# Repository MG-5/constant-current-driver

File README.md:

# constant-current-driver
A constant current driver up to 1.5A to drive LEDs

### Requirements for rev 1.0
* efficient step-down converter, not linear
* high frequency
* cheap IC
* PWM control
* up to 1.5A in voltage range 5-24V output

### Known issues in rev 1.0
* none

### Pictures (rev 1.0)

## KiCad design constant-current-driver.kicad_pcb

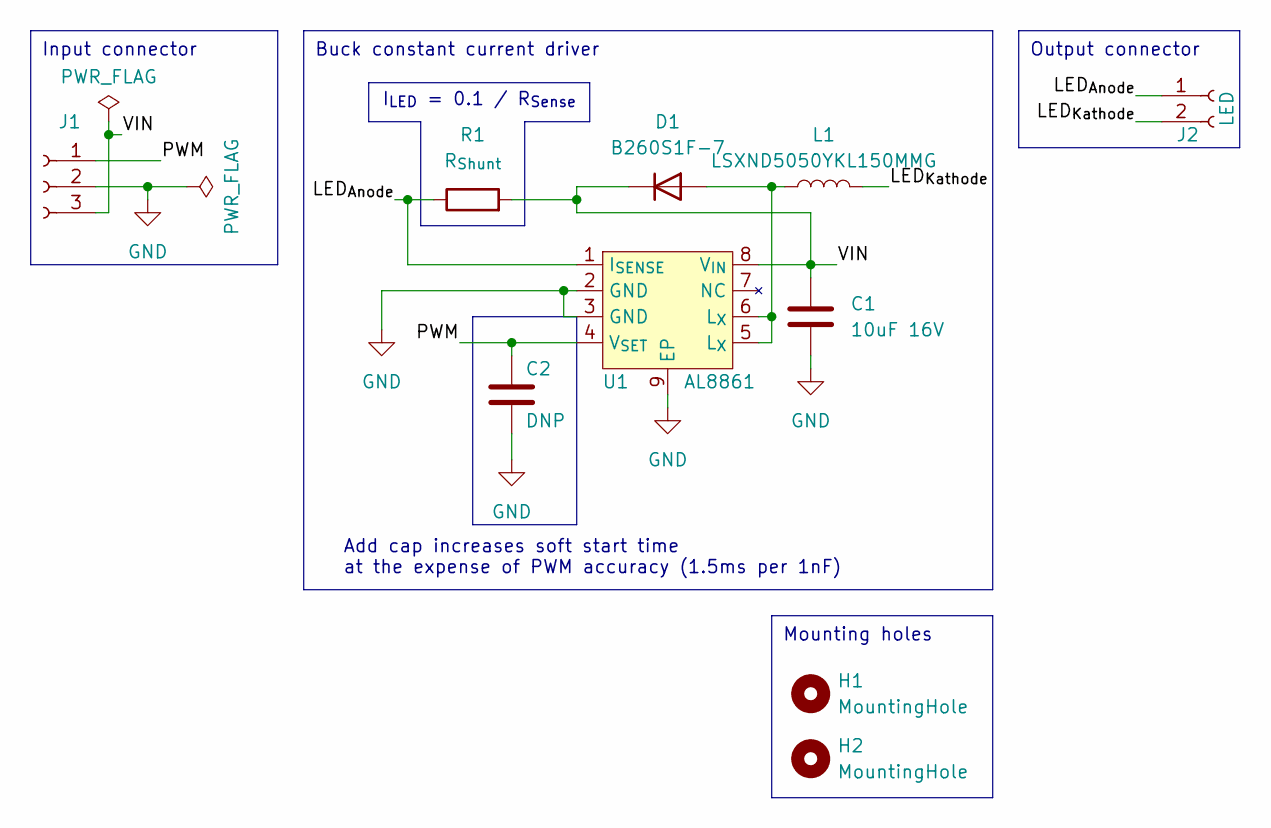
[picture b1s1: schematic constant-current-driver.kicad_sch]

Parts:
C1: 10uF 16V; C_0805_2012Metric
C2: DNP; C_0603_1608Metric
D1: B260S1F-7; D_SOD-123
H1, H2: MountingHole; MountingHole_3.2mm_M3_ISO14580
J1: Conn; PinHeader_1x03_P2.54mm_Horizontal
J2: LED; PinHeader_1x02_P2.54mm_Horizontal
L1: LSXND5050YKL150MMG; L_Taiyo-Yuden_MD-5050
R1: R_{Shunt}; R_0805_2012Metric
U1: AL8861; MSOP-8-1EP_3x3mm_P0.65mm_EP1.5x1.8mm_ThermalVias

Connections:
/LED_{Anode}: J2.1, R1.1, U1.1 (I_{SENSE})
/LED_{Kathode}: J2.2, L1.2
/PWM: C2.1, J1.1, U1.4 (V_{SET})
/VIN: C1.1, D1.1 (K), J1.3, R1.2, U1.8 (V_{IN})
GND: C1.2, C2.2, J1.2, U1.2 (GND), U1.3 (GND), U1.9 (EP)
unnamed: D1.2 (A), L1.1, U1.5 (L_{X}), U1.6 (L_{X})

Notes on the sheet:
Buck constant current driver
Output connector
Mounting holes
Input connector
I_{LED} = 0.1 / R_{Sense}
Add cap increases soft start time at the expense of PWM accuracy (1.5ms per 1nF)

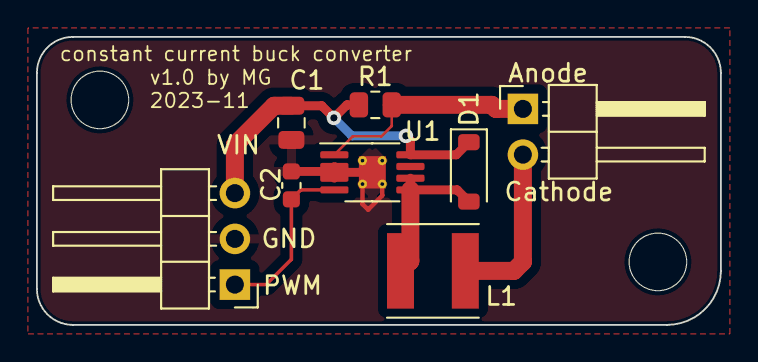
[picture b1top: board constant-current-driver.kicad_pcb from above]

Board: 2 copper layers, 38.0 x 16.0 mm, 10 parts (0 on the bottom side), 6 nets.

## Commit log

2023-11-11 Create schematic and PCB
